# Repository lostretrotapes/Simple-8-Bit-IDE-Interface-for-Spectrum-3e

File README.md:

# Simple-8-Bit-IDE-Interface-for-Spectrum-3e

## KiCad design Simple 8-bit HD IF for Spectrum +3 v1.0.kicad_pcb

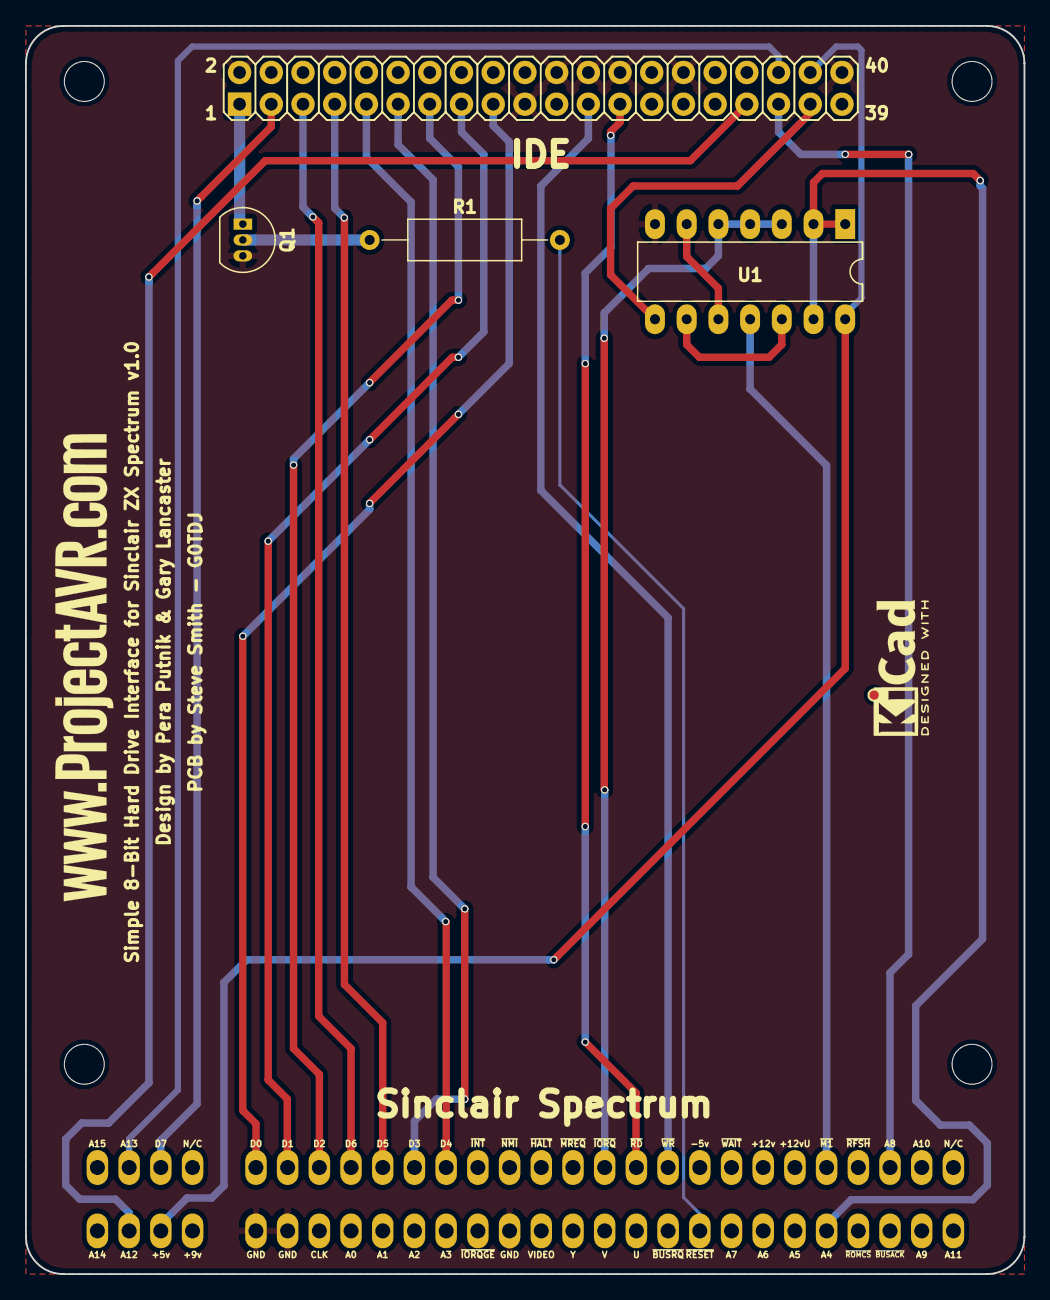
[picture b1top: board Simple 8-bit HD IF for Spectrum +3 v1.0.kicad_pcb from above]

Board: 2 copper layers, 80.0 x 100.0 mm, 5 parts (0 on the bottom side), 24 nets.

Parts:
P1: SPECTRUM_EDGE-28x2; Spectrum_Edge_Connector
P2: CONN_20X2; Header-2X20
Q1: BC327; TO-92_Inline_Narrow_Oval
R1: 100K; R_Axial_DIN0309_L9.0mm_D3.2mm_P15.24mm_Horizontal
U1: 74LS10; DIP-14_W7.62mm_LongPads

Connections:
+5volts: P1.3B, P2.38, U1.14
A4: P1.24B, U1.1, U1.2, U1.13
A8: P1.26A, P2.35
A12: P1.2B, P2.33
A13: P1.2A, P2.36
D0: P1.6A, P2.17
D1: P1.7A, P2.15
D2: P1.8A, P2.13
D3: P1.11A, P2.11
D4: P1.12A, P2.9
D5: P1.10A, P2.7
D6: P1.9A, P2.5
D7: P1.3A, P2.3
GND: P1.6B, P1.7B, P1.14B, P2.2, P2.19, P2.22, P2.24, P2.26, P2.30, P2.40, Q1.3, U1.7
unnamed: Q1.2, R1.1
unnamed: U1.6, U1.10
unnamed: U1.9, U1.12
~CS0: P2.37, U1.8
~IOR: P1.18A, P2.25
~IORQ: P1.17A, U1.3, U1.4, U1.5
~IOW: P1.19A, P2.23
~I_RESET: P2.1, Q1.1
~M1: P1.24A, U1.11
~RESET: P1.20B, R1.2
